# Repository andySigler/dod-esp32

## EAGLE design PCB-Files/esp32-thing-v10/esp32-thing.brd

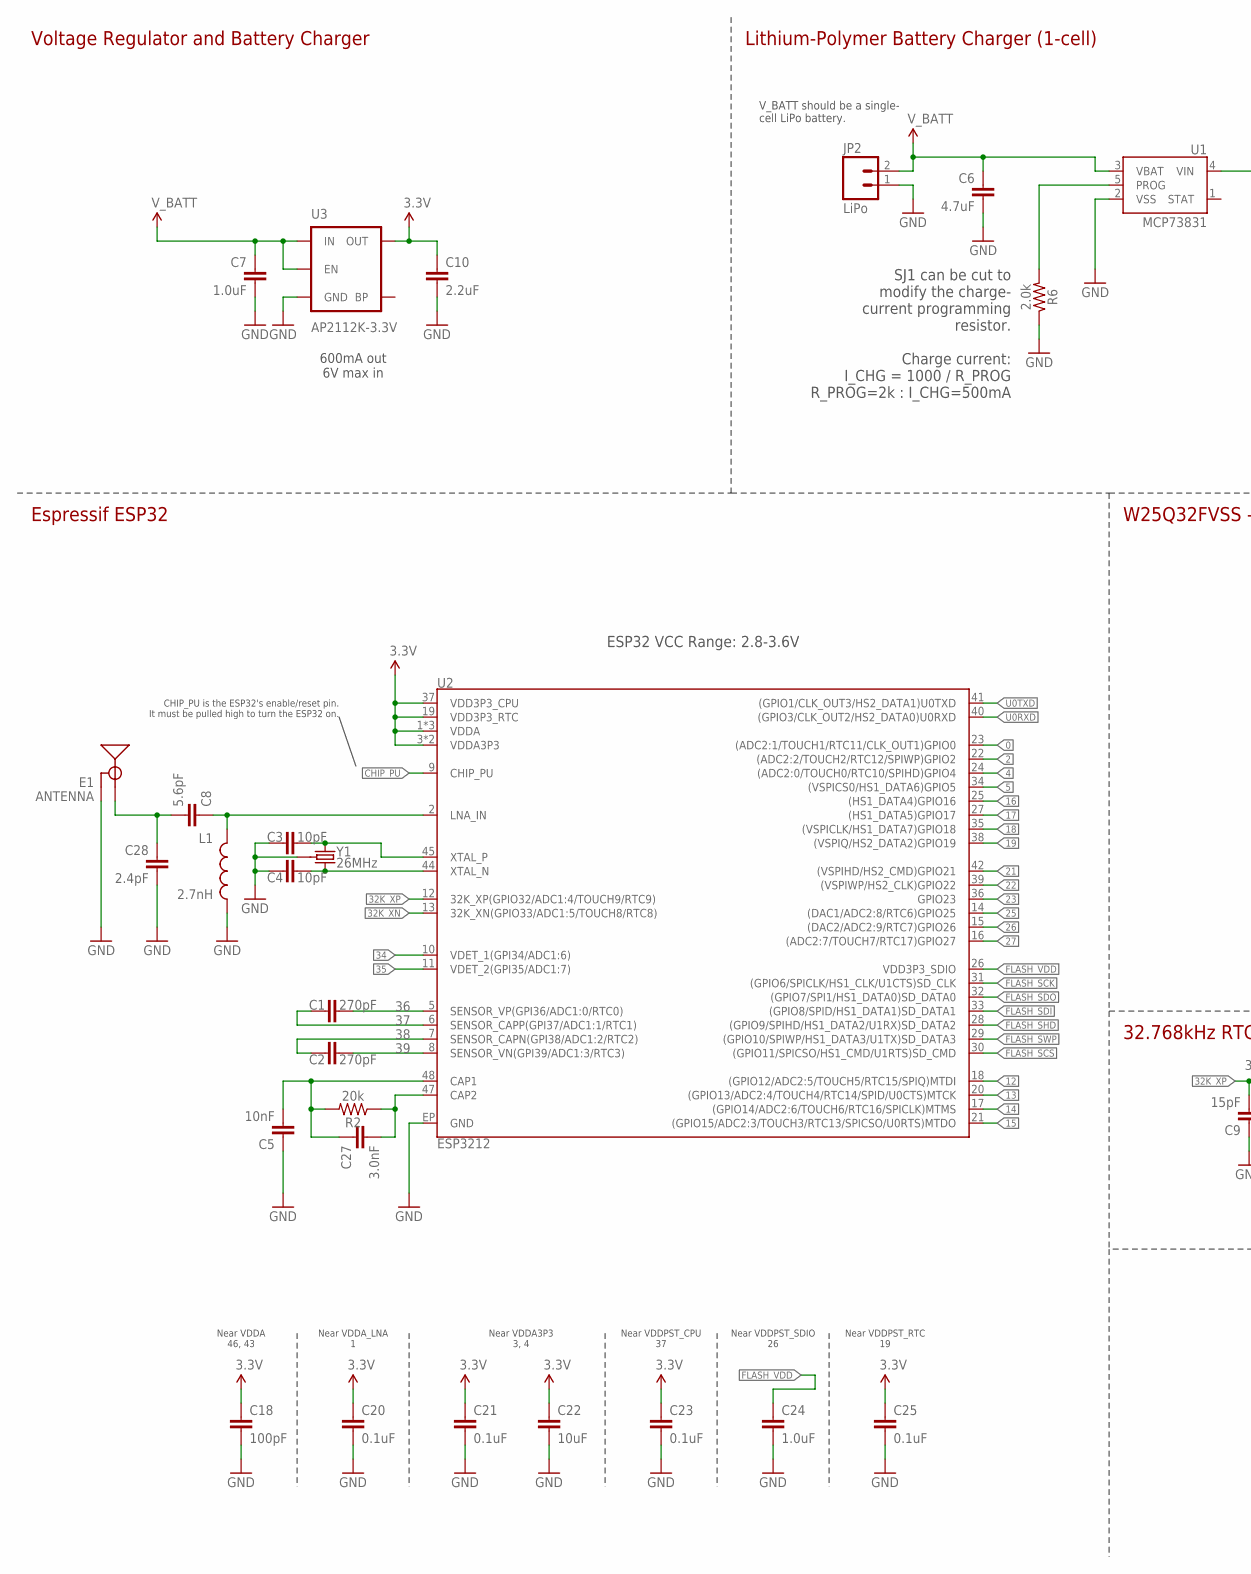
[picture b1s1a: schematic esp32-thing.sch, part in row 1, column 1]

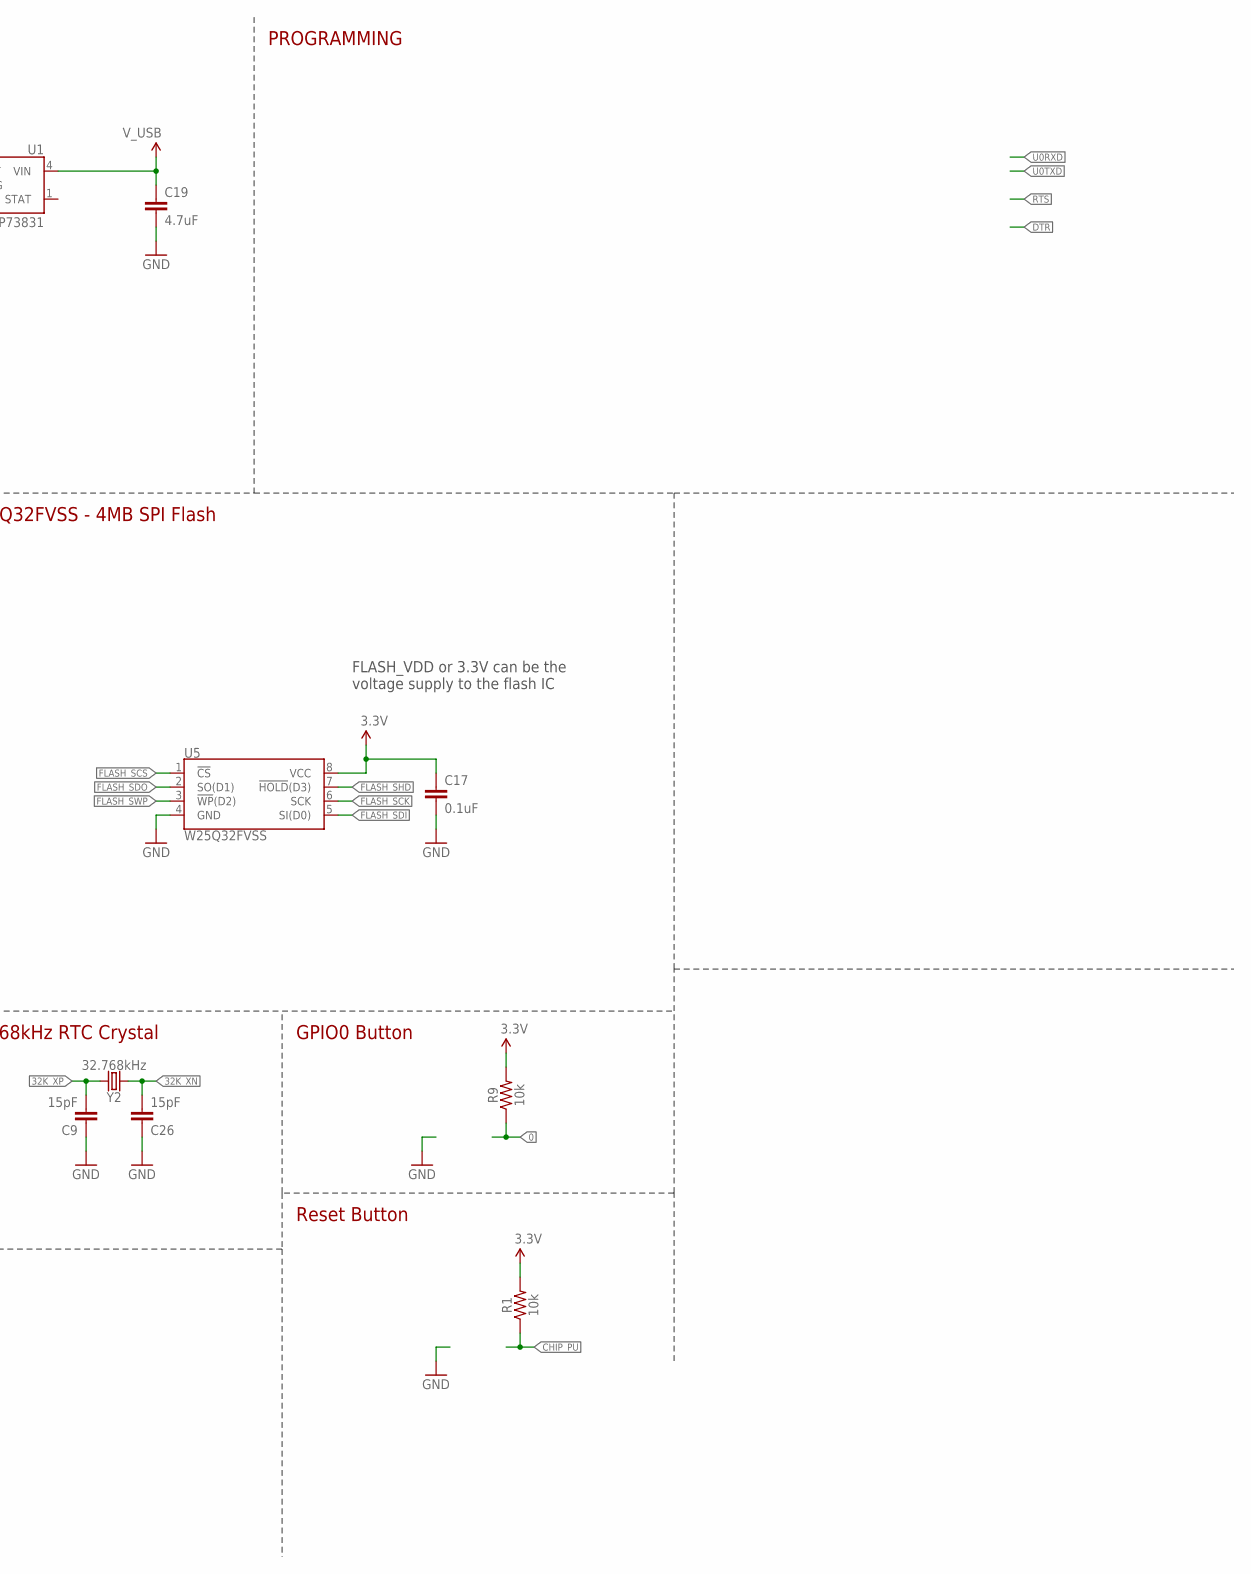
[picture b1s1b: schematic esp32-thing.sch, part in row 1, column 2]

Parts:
C1, C2: 270pF; 0603
C3, C4: 10pF; 0603
C5: 10nF; 0603
C6, C19: 4.7uF; 0603
C7: 1.0uF; 0805
C8: 5.6pF; 0603
C9, C26: 15pF; 0603
C10: 2.2uF; 0603
C17, C20, C21, C23, C25: 0.1uF; 0603
C18: 100pF; 0603
C22: 10uF; 0603
C24: 1.0uF; 0603
C27: 3.0nF; 0603
C28: 2.4pF; 0603
E1: ANTENNA; TRACE_ANTENNA_2.4GHZ_25.7MM_TUNED
JP2: LiPo; JST-2-PTH
L1: 2.7nH; 0603
R1, R9: 10k; 0603
R2: 20k; 0603
R6: 2.0k; 0603
U1: MCP73831; SOT23-5
U2: ESP3212; QFN48-0.4MM
U3: AP2112K-3.3V; SOT23-5
U5: W25Q32FVSS; SOIC-8
Y1: 26MHz; CRYSTAL-SMD-3.2X2.5
Y2: 32.768kHz; CRYSTAL-SMD-3.2X1.5MM

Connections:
0: R9.1, U2.23 ((ADC2:1/TOUCH1/RTC11/CLK_OUT1)GPIO0)
2: U2.22 ((ADC2:2/TOUCH2/RTC12/SPIWP)GPIO2)
3.3V: C10.1, C17.1, C18.1, C20.1, C21.1, C22.1, C23.1, C25.1, R1.2, R9.2, U2.1 (VDDA), U2.3 (VDDA3P3), U2.4 (VDDA3P3), U2.19 (VDD3P3_RTC), U2.37 (VDD3P3_CPU), U2.43 (VDDA), U2.46 (VDDA), U3.5 (OUT), U5.8 (VCC)
4: U2.24 ((ADC2:0/TOUCH0/RTC10/SPIHD)GPIO4)
5: U2.34 ((VSPICS0/HS1_DATA6)GPIO5)
12: U2.18 ((GPIO12/ADC2:5/TOUCH5/RTC15/SPIQ)MTDI)
13: U2.20 ((GPIO13/ADC2:4/TOUCH4/RTC14/SPID/U0CTS)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)
14: U2.17 ((GPIO14/ADC2:6/TOUCH6/RTC16/SPICLK)MTMS)
15: U2.21 ((GPIO15/ADC2:3/TOUCH3/RTC13/SPICSO/U0RT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)
16: U2.25 ((HS1_DATA4)GPIO16)
17: U2.27 ((HS1_DATA5)GPIO17)
18: U2.35 ((VSPICLK/HS1_DATA7)GPIO18)
19: U2.38 ((VSPIQ/HS2_DATA2)GPIO19)
21: U2.42 ((VSPIHD/HS2_CMD)GPIO21)
22: U2.39 ((VSPIWP/HS2_CLK)GPIO22)
23: U2.36 (GPIO23)
25: U2.14 ((DAC1/ADC2:8/RTC6)GPIO25)
26: U2.15 ((DAC2/ADC2:9/RTC7)GPIO26)
27: U2.16 ((ADC2:7/TOUCH7/RTC17)GPIO27)
32K_XN: C26.2, U2.13 (32K_XN(GPIO33/ADC1:5/TOUCH8/RTC8)), Y2.P$2 (2)
32K_XP: C9.2, U2.12 (32K_XP(GPIO32/ADC1:4/TOUCH9/RTC9)), Y2.P$1 (1)
34: U2.10 (VDET_1(GPI34/ADC1:6))
35: U2.11 (VDET_2(GPI35/ADC1:7))
36: C1.2, U2.5 (SENSOR_VP(GPI36/ADC1:0/RTC0))
37: C1.1, U2.6 (SENSOR_CAPP(GPI37/ADC1:1/RTC1))
38: C2.1, U2.7 (SENSOR_CAPN(GPI38/ADC1:2/RTC2))
39: C2.2, U2.8 (SENSOR_VN(GPI39/ADC1:3/RTC3))
CAP_10N: C5.2, C27.1, R2.2, U2.48 (CAP1)
CHIP_PU: R1.1, U2.9 (CHIP_PU)
FLASH_SCK: U2.31 ((GPIO6/SPICLK/HS1_CLK/U1CTS)SD_CLK), U5.6 (SCK)
FLASH_SCS: U2.30 ((GPIO11/SPICSO/HS1_CMD/U1RTS)SD_CMD), U5.1 (!CS!)
FLASH_SDI: U2.33 ((GPIO8/SPID/HS1_DATA1)SD_DATA1), U5.5 (SI(D0))
FLASH_SDO: U2.32 ((GPIO7/SPI1/HS1_DATA0)SD_DATA0), U5.2 (SO(D1))
FLASH_SHD: U2.28 ((GPIO9/SPIHD/HS1_DATA2/U1RX)SD_DATA2), U5.7 (!HOLD!(D3))
FLASH_SWP: U2.29 ((GPIO10/SPIWP/HS1_DATA3/U1TX)SD_DATA3), U5.3 (!WP!(D2))
FLASH_VDD: C24.1, U2.26 (VDD3P3_SDIO)
GND: C3.1, C4.1, C5.1, C6.2, C7.2, C9.1, C10.2, C17.2, C18.2, C19.2, C20.2, C21.2, C22.2, C23.2, C24.2, C25.2, C26.1, C28.2, E1.GND, E1.GND2 (GND), JP2.1, L1.2, R6.1, U1.2 (VSS), U2.EP (GND), U3.2 (GND), U5.4 (GND), Y1.2 (GND), Y1.4 (GND)
LNA_IN: C8.1, L1.1, U2.2 (LNA_IN)
unnamed: C27.2, R2.1, U2.47 (CAP2)
unnamed: C3.2, U2.45 (XTAL_P), Y1.1
unnamed: R6.2, U1.5 (PROG)
unnamed: C4.2, U2.44 (XTAL_N), Y1.3 (2)
TRACE_ANT: C8.2, C28.1, E1.ANT (SIGNAL)
U0RXD: U2.40 ((GPIO3/CLK_OUT2/HS2_DATA0)U0RXD)
U0TXD: U2.41 ((GPIO1/CLK_OUT3/HS2_DATA1)U0TXD)
V_BATT: C6.1, C7.1, JP2.2, U1.3 (VBAT), U3.1 (IN), U3.3 (EN)
V_USB: C19.1, U1.4 (VIN)

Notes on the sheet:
PROGRAMMING
V_BATT should be a single- cell LiPo battery.
Charge current: I_CHG = 1000 / R_PROG R_PROG=2k : I_CHG=500mA
Voltage Regulator and Battery Charger
SJ1 can be cut to modify the charge- current programming resistor.
Lithium-Polymer Battery Charger (1-cell)
600mA out 6V max in
Near VDDA 46, 43
Near VDDA_LNA 1
Near VDDA3P3 3, 4
Near VDDPST_CPU 37
Near VDDPST_SDIO 26
Near VDDPST_RTC 19
Espressif ESP32
W25Q32FVSS - 4MB SPI Flash
32.768kHz RTC Crystal
GPIO0 Button
Reset Button
ESP32 VCC Range: 2.8-3.6V
FLASH_VDD or 3.3V can be the voltage supply to the flash IC
CHIP_PU is the ESP32's enable/reset pin. It must be pulled high to turn the ESP32 on.

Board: 2 copper layers, 35 parts (0 on the bottom side), 26 nets, no tracks yet.

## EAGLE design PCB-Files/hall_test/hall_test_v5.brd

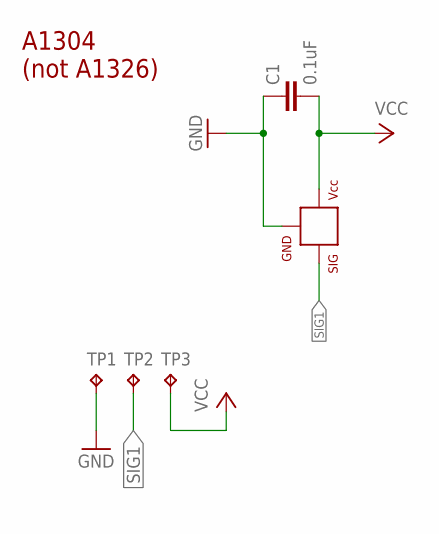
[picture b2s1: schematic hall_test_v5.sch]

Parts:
C1: 0.1uF; 0603-CAP
HALL: HALLEFFECT-A1326; SOT23-3
TP1, TP2, TP3: TPTP10SQ; TP10SQ

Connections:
GND: C1.1, HALL.3 (GND), TP1.TP
SIG1: HALL.2 (SIG), TP2.TP
VCC: C1.2, HALL.1 (VCC), TP3.TP

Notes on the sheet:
A1304 (not A1326)

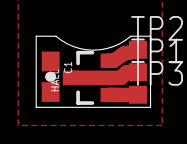
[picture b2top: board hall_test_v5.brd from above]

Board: 2 copper layers, 6.3 x 4.0 mm, 5 parts (0 on the bottom side), 3 nets.

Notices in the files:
parts and their libraries:
SparkFun-Resistors: Licensing: Creative Commons ShareAlike 4.0 International - https://creativecommons.org/licenses/by-sa/4.0
SparkFun-DigitalIC: Licensing: CC v3.0 Share-Alike You are welcome to use this library for commercial purposes.
